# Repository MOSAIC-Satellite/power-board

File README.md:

# Power Board

This is the repository for MOSAIC's Power Board.

For detailed information on the Power Board, check out its core documentation [here](https://www.mosaicsat.org/core_documentation/hardware/power_board/).

To get your own MOSAIC Power Board, visit the MOSAIC fabrication guide [here](https://www.mosaicsat.org/getting_mosaic/).

## Current Features

*Newest board version: 2.0*

| **Feature** |
| :----------- |
| 6x high-side DC sensors for solar cells |
| LiPo battery high side DC sensor |
| Single-cell LiPo battery charger circuit |
| 12x  2mm JST solar cell input jacks|
| 2x 2mm JST battery input jacks |
| LiPo battery overcharge protection |
| Solar cell reverse current protection |
| 2x Qwiic connectors for I2C connection to Main Board |

## Planned Changes

The following are the current plans for changes to MOSAIC's Power Board. 

- The current version of MOSAIC's Power Board is designed to be used with only a single-cell LiPo battery like [this one](https://www.sparkfun.com/lithium-ion-battery-2ah.html). Future iterations of the Power Board should include the option to utilize different energy storage methods, such as AA and 18650 batteries. This, of course, will require a different charger circuit for each method, so the board may include a new slot where users can plug in their preferred power charger circuit. 

## Change Log

You can find the change log for the Power Board on MOSAIC's website [here](https://www.mosaicsat.org/core_documentation/hardware/power_board/change_log/).

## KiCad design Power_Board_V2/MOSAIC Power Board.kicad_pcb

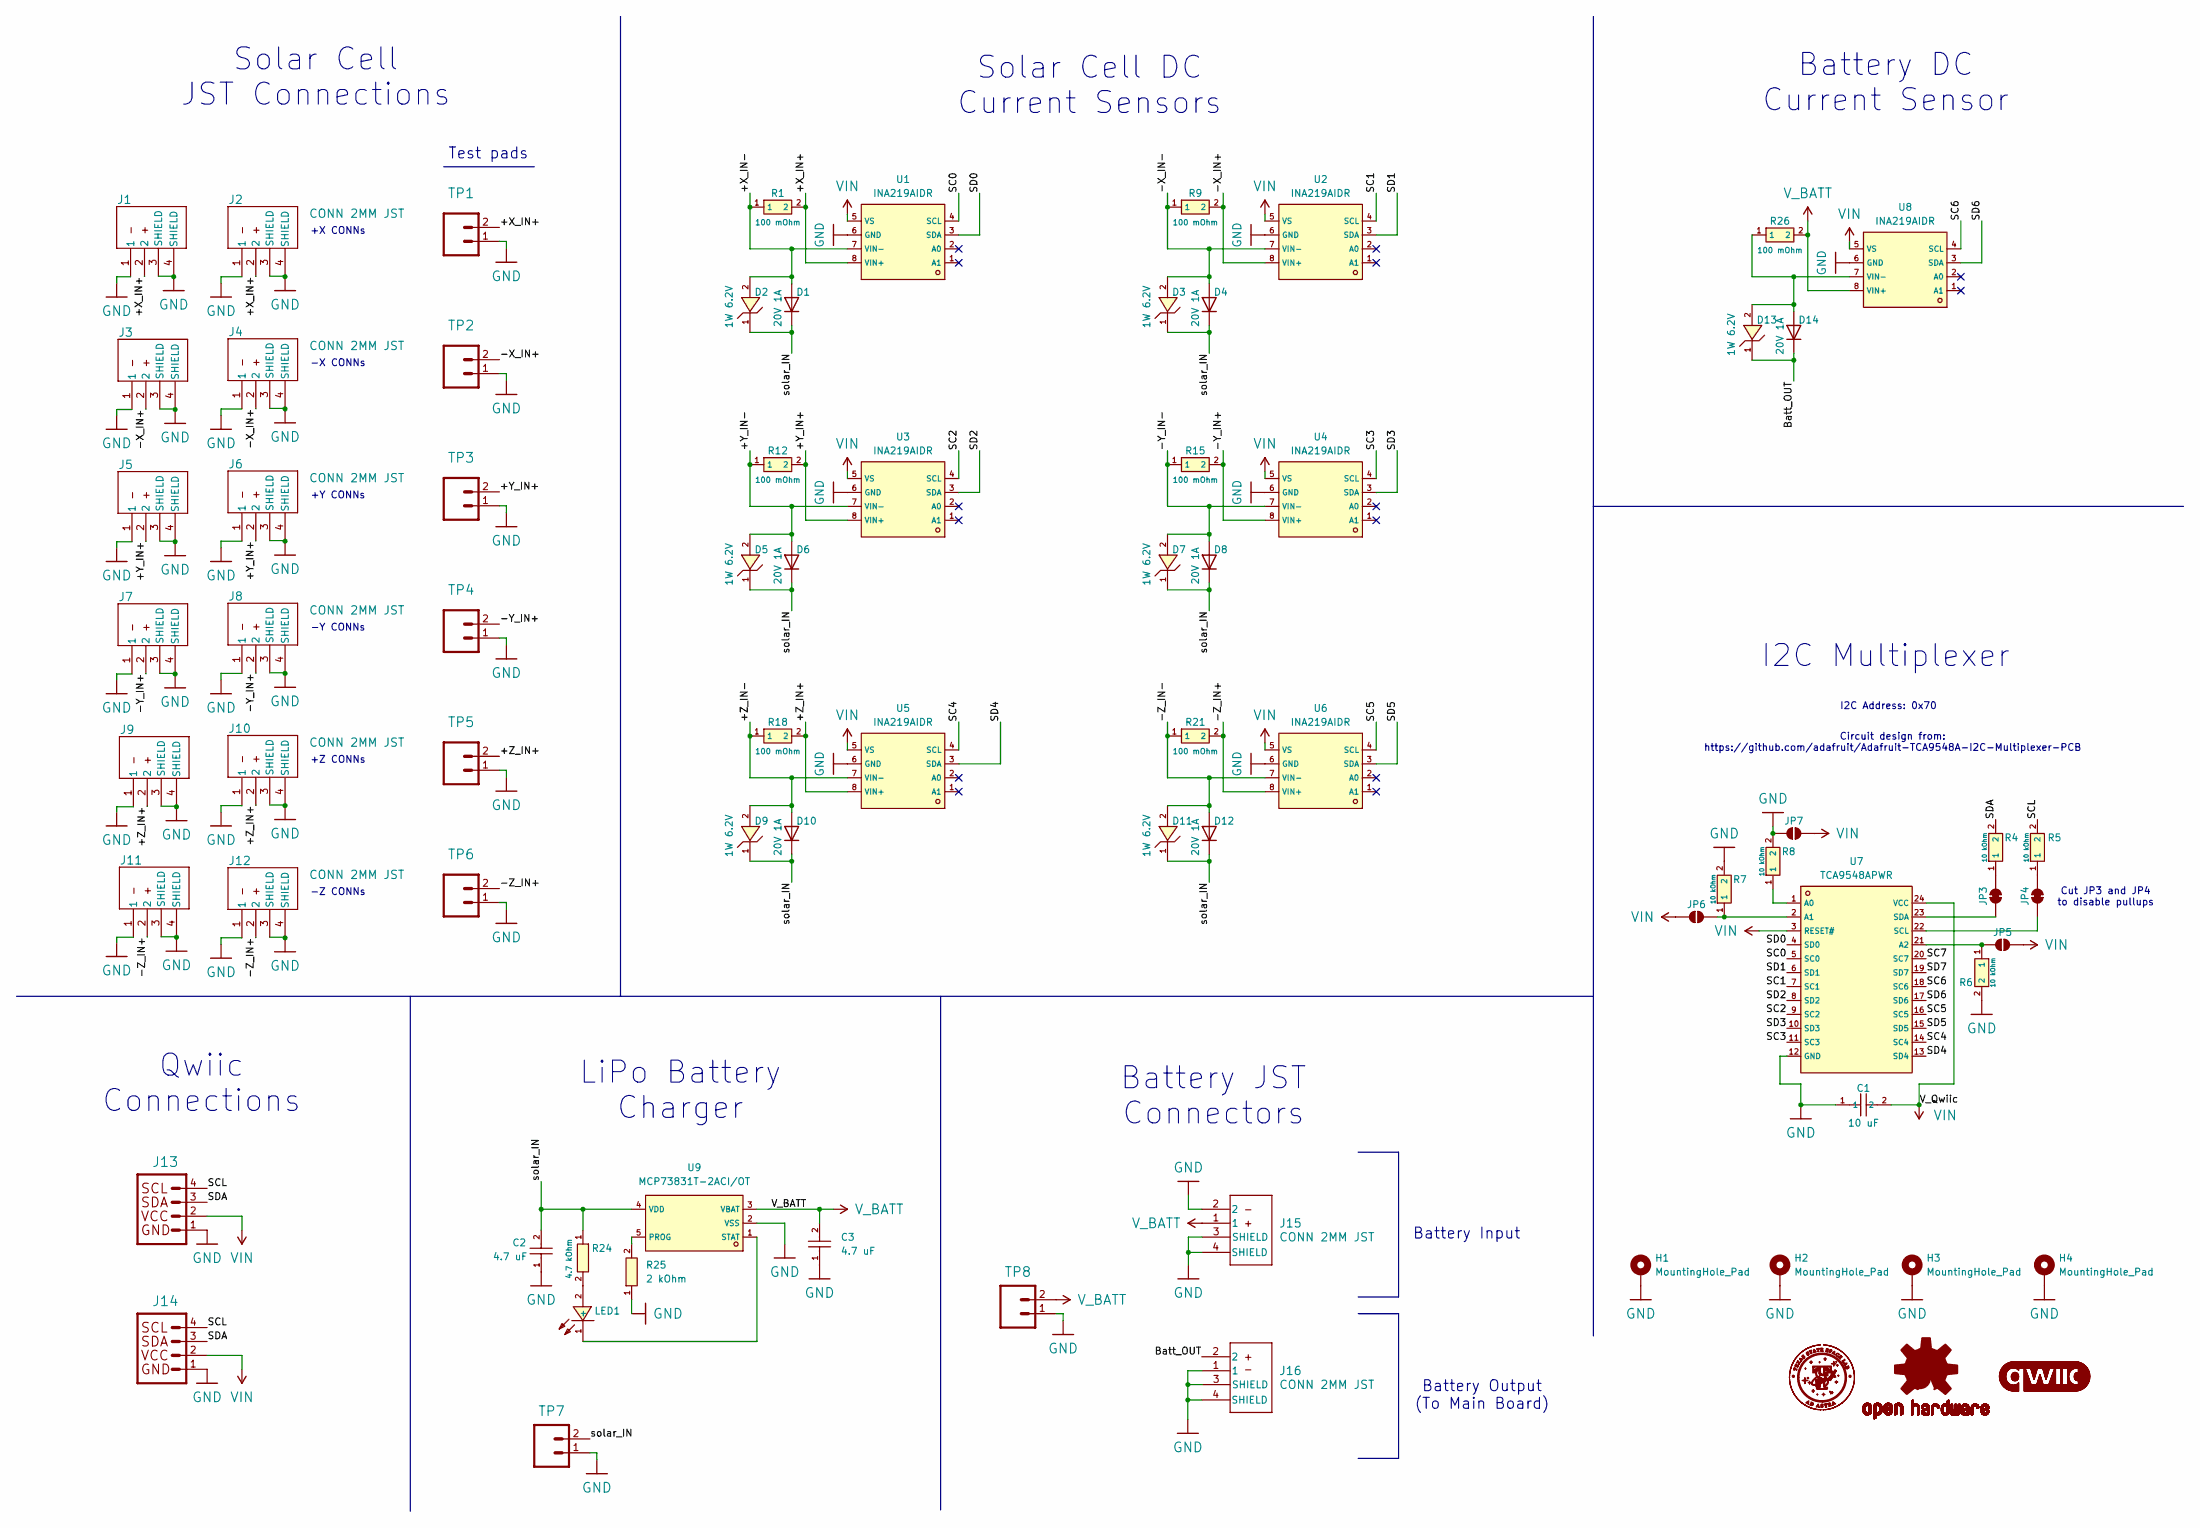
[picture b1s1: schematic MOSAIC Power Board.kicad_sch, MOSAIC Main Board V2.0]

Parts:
C1: 10 uF; C_0603; LCSC C1691
C2, C3: 4.7 uF; C_0603; LCSC C1705
D1, D4, D6, D8, D10, D12, D14: 20V 1A; D_SOD-323; JLCPCB Part # C41424805
D2, D3, D5, D7, D9, D11, D13: 1W 6.2V; Z_DO-214AC; LCSC C151039
H1, H2: MountingHole_Pad; MountingHole_3.2mm_Pad_Oval
H3, H4: MountingHole_Pad; MountingHole_3.2mm_M3_Pad
J1, J2, J3, J4, J5, J6, J7, J8, J9, J10, J11, J12, J15, J16: CONN 2MM JST; CONN_2mm_JST; JLCPCB Part # C295747
J13, J14: QWIIC_CONN_RA; JLCPCB Part # C145956
JP3, JP4: SolderJumper_2_Bridged; SolderJumper-2_P1.3mm_Bridged_RoundedPad1.0x1.5mm
JP5, JP6, JP7: SolderJumper_2_Open; SolderJumper-2_P1.3mm_Open_RoundedPad1.0x1.5mm
LED1: LED_0603; LCSC C125095
LOGO1: OSHW-LOGO-L
LOGO2, LOGO3: QWIIC_logo_8MM
R1, R9, R12, R15, R18, R21, R26: 100 mOhm; R_shunt; LCSC C346817
R4, R5, R6, R7, R8: 10 kOhm; R_0805; LCSC C5123591
R24: 4.7 kOhm; R_0603; LCSC C22874
R25: 2 kOhm; R_0603; LCSC C22975
TP1, TP2, TP3, TP4, TP5, TP6, TP7, TP8: 1X02_NO_SILK
U1, U2, U3, U4, U5, U6, U8: INA219AIDR; LCSC C138706
U7: TCA9548APWR; LCSC C130026
U9: MCP73831T-2ACI/OT; MCP73831_IC_BATT_CNTL; LCSC C424093

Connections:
/+X_IN+: J1.2, J2.2, R1.2, TP1.2, U1.8 (VIN+)
/+X_IN-: D1.2 (A), D2.2, R1.1, U1.7 (VIN-)
/+Y_IN+: J5.2, J6.2, R12.2, TP3.2, U3.8 (VIN+)
/+Y_IN-: D5.2, D6.2 (A), R12.1, U3.7 (VIN-)
/+Z_IN+: J9.2, J10.2, R18.2, TP5.2, U5.8 (VIN+)
/+Z_IN-: D9.2, D10.2 (A), R18.1, U5.7 (VIN-)
/-X_IN+: J3.2, J4.2, R9.2, TP2.2, U2.8 (VIN+)
/-X_IN-: D3.2, D4.2 (A), R9.1, U2.7 (VIN-)
/-Y_IN+: J7.2, J8.2, R15.2, TP4.2, U4.8 (VIN+)
/-Y_IN-: D7.2, D8.2 (A), R15.1, U4.7 (VIN-)
/-Z_IN+: J11.2, J12.2, R21.2, TP6.2, U6.8 (VIN+)
/-Z_IN-: D11.2, D12.2 (A), R21.1, U6.7 (VIN-)
/Batt_OUT: D13.1, D14.1 (K), J16.2
/SC0: U1.4 (SCL), U7.5 (SC0)
/SC1: U2.4 (SCL), U7.7 (SC1)
/SC2: U3.4 (SCL), U7.9 (SC2)
/SC3: U4.4 (SCL), U7.11 (SC3)
/SC4: U5.4 (SCL), U7.14 (SC4)
/SC5: U6.4 (SCL), U7.16 (SC5)
/SC6: U7.18 (SC6), U8.4 (SCL)
/SC7: U7.20 (SC7)
/SCL: J13.4, J14.4, R5.2
/SD0: U1.3 (SDA), U7.4 (SD0)
/SD1: U2.3 (SDA), U7.6 (SD1)
/SD2: U3.3 (SDA), U7.8 (SD2)
/SD3: U4.3 (SDA), U7.10 (SD3)
/SD4: U5.3 (SDA), U7.13 (SD4)
/SD5: U6.3 (SDA), U7.15 (SD5)
/SD6: U7.17 (SD6), U8.3 (SDA)
/SD7: U7.19 (SD7)
/SDA: J13.3, J14.3, R4.2
/solar_IN: C2.2, D1.1 (K), D2.1, D3.1, D4.1 (K), D5.1, D6.1 (K), D7.1, D8.1 (K), D9.1, D10.1 (K), D11.1, D12.1 (K), R24.1, TP7.2, U9.4 (VDD)
GND: C1.1, C2.1, C3.1, H1.1, H2.1, H3.1, H4.1, J1.1, J1.3 (SHIELD), J1.4 (SHIELD), J2.1, J2.3 (SHIELD), J2.4 (SHIELD), J3.1, J3.3 (SHIELD), J3.4 (SHIELD), J4.1, J4.3 (SHIELD), J4.4 (SHIELD), J5.1, J5.3 (SHIELD), J5.4 (SHIELD), J6.1, J6.3 (SHIELD), J6.4 (SHIELD), J7.1, J7.3 (SHIELD), J7.4 (SHIELD), J8.1, J8.3 (SHIELD), J8.4 (SHIELD), J9.1, J9.3 (SHIELD), J9.4 (SHIELD), J10.1, J10.3 (SHIELD), J10.4 (SHIELD), J11.1, J11.3 (SHIELD), J11.4 (SHIELD), J12.1, J12.3 (SHIELD), J12.4 (SHIELD), J13.1, J14.1, J15.2, J15.3 (SHIELD), J15.4 (SHIELD), J16.1, J16.3 (SHIELD), J16.4 (SHIELD), JP7.1 (A), R6.2, R7.2, R8.2, R25.1, TP1.1, TP2.1, TP3.1, TP4.1, TP5.1, TP6.1, TP7.1, TP8.1, U1.6 (GND), U2.6 (GND), U3.6 (GND), U4.6 (GND), U5.6 (GND), U6.6 (GND), U7.12 (GND), U8.6 (GND), U9.2 (VSS)
unnamed: D13.2, D14.2 (A), R26.1, U8.7 (VIN-)
unnamed: JP3.1 (A), U7.23 (SDA)
unnamed: JP3.2 (B), R4.1
unnamed: JP4.1 (A), U7.22 (SCL)
unnamed: JP4.2 (B), R5.1
unnamed: JP5.1 (A), R6.1, U7.21 (A2)
unnamed: JP6.2 (B), R7.1, U7.2 (A1)
unnamed: LED1.2 (+), R24.2
unnamed: LED1.1 (-), U9.1 (STAT)
unnamed: R8.1, U7.1 (A0)
unnamed: R25.2, U9.5 (PROG)
VIN: C1.2, J13.2, J14.2, JP5.2 (B), JP6.1 (A), JP7.2 (B), U1.5 (VS), U2.5 (VS), U3.5 (VS), U4.5 (VS), U5.5 (VS), U6.5 (VS), U7.3 (RESET#), U7.24 (VCC), U8.5 (VS)
V_BATT: C3.2, J15.1, R26.2, TP8.2, U8.8 (VIN+), U9.3 (VBAT)

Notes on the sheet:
Battery Input
-Z CONNs
Battery JST Connectors
Solar Cell JST Connections
Test pads
I2C Multiplexer
-Y CONNs
Circuit design from: https://github.com/adafruit/Adafruit-TCA9548A-I2C-Multiplexer-PCB
+Z CONNs
Battery DC Current Sensor
Qwiic Connections
+X CONNs
+Y CONNs
I2C Address: 0x70
Cut JP3 and JP4 to disable pullups
LiPo Battery Charger
-X CONNs
Battery Output (To Main Board)
Solar Cell DC Current Sensors

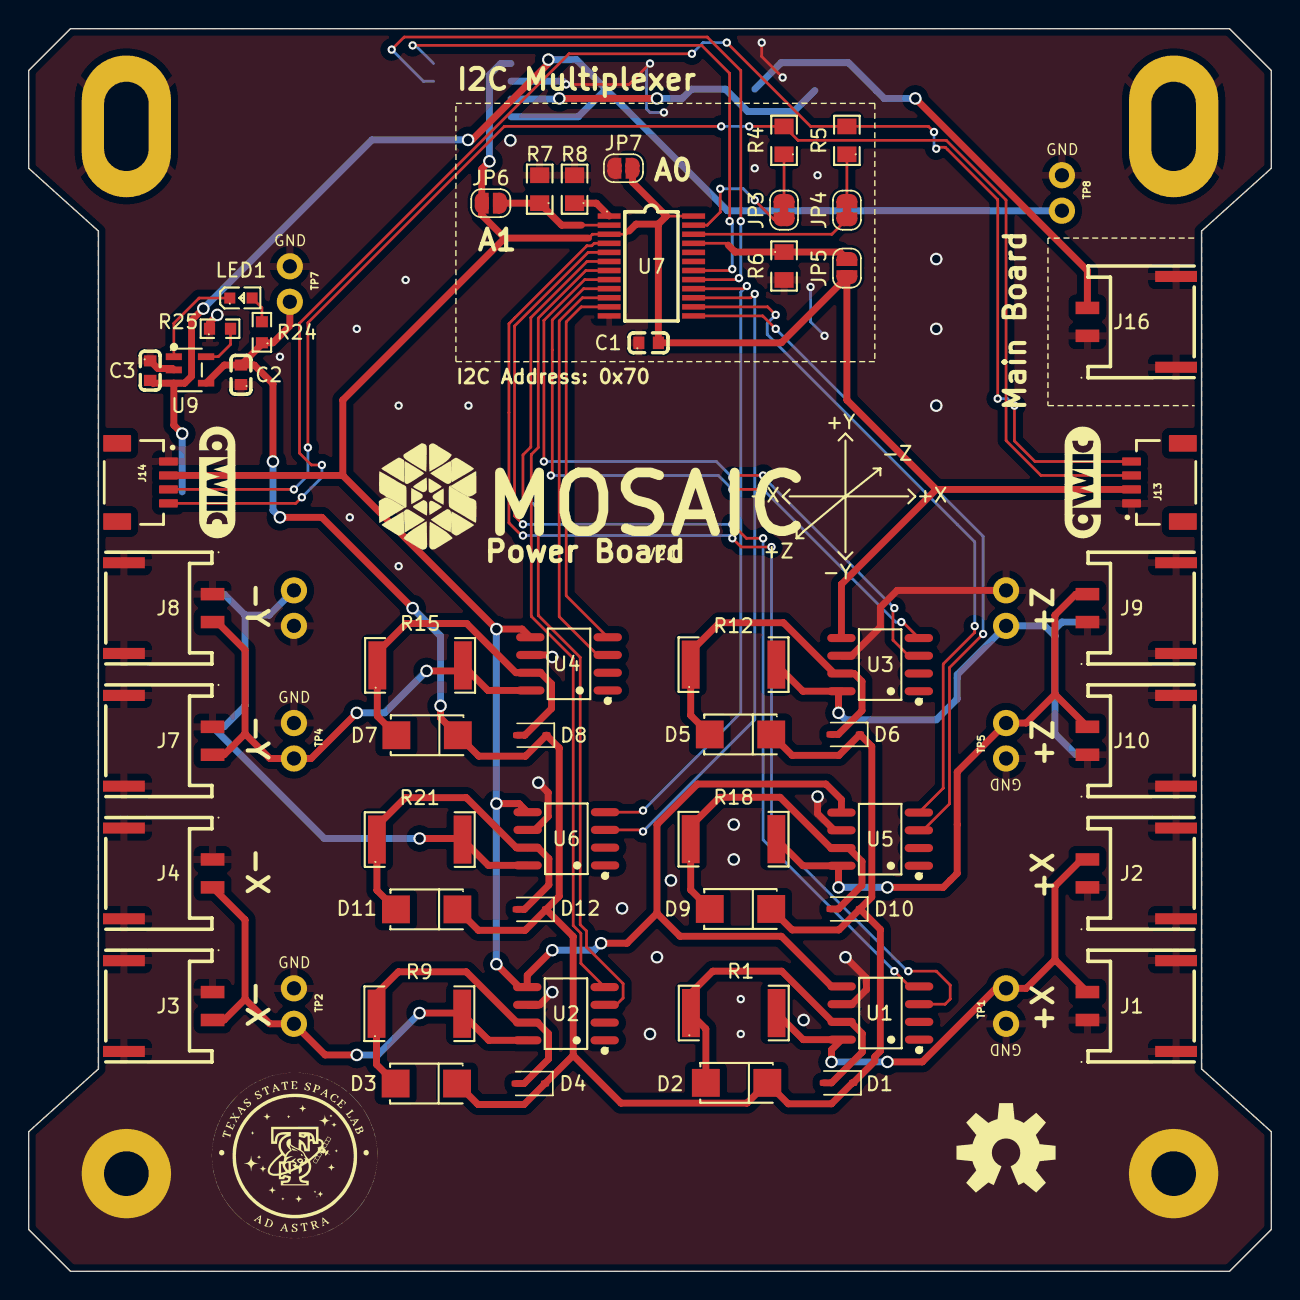
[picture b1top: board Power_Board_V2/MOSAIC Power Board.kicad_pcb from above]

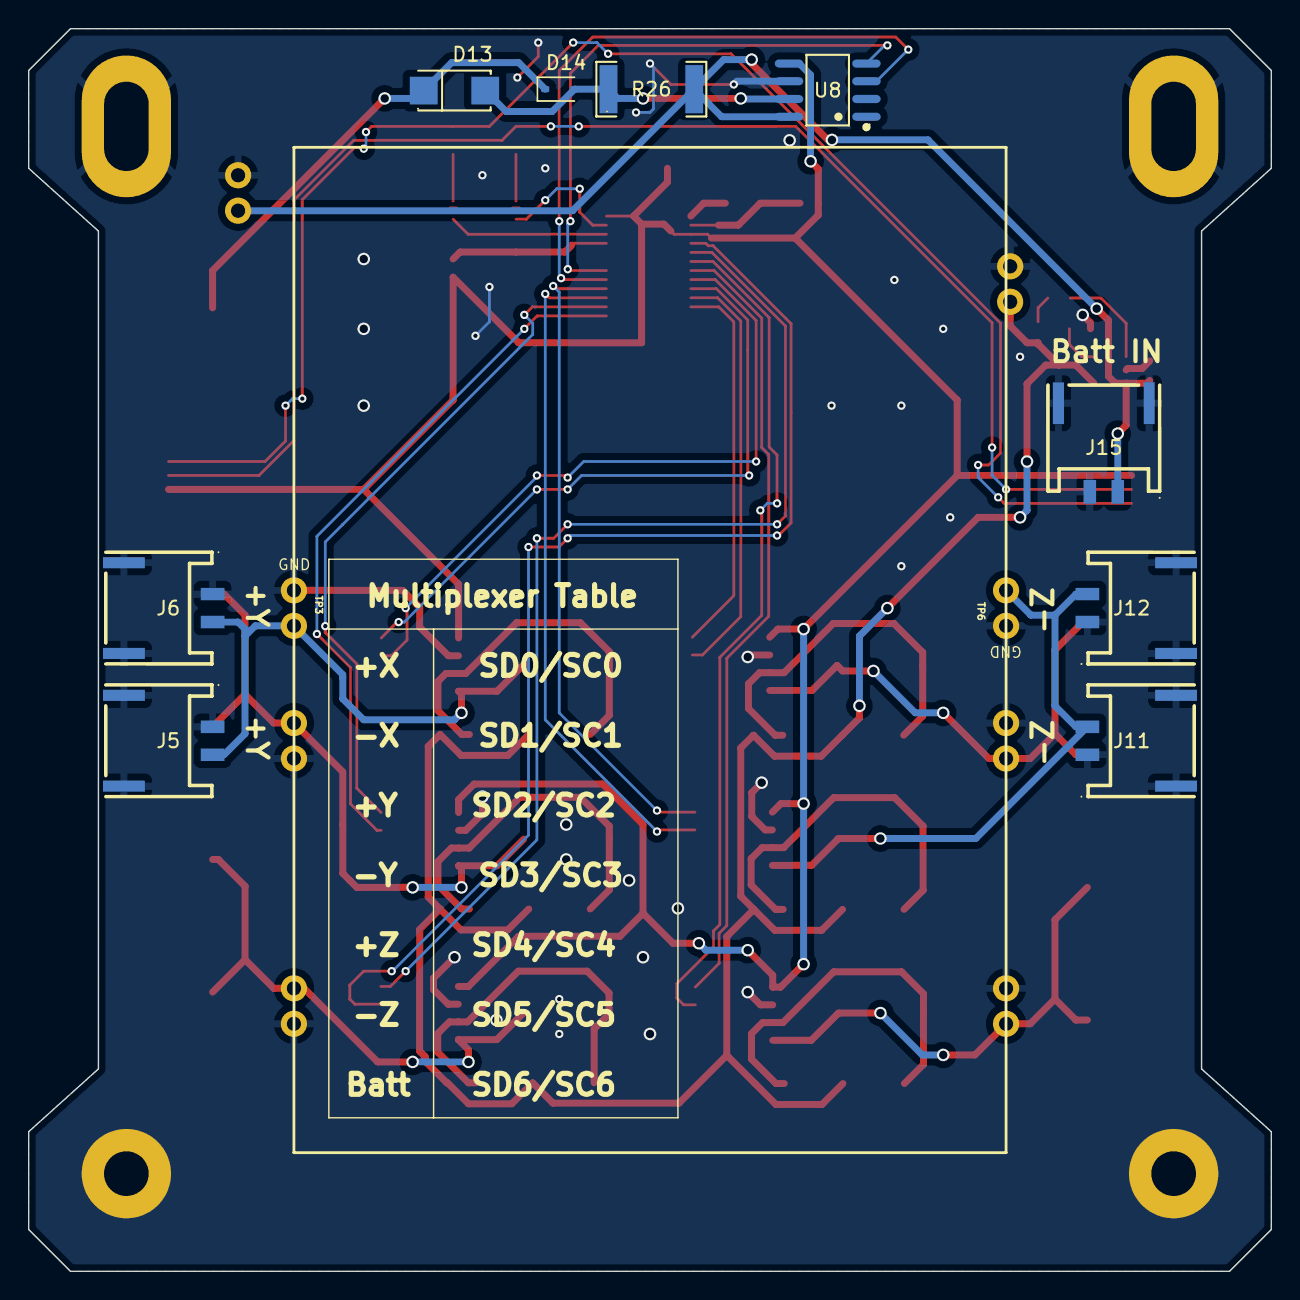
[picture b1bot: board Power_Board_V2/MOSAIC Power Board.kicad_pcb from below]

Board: 2 copper layers, 89.0 x 89.0 mm, 77 parts (11 on the bottom side), 44 nets.

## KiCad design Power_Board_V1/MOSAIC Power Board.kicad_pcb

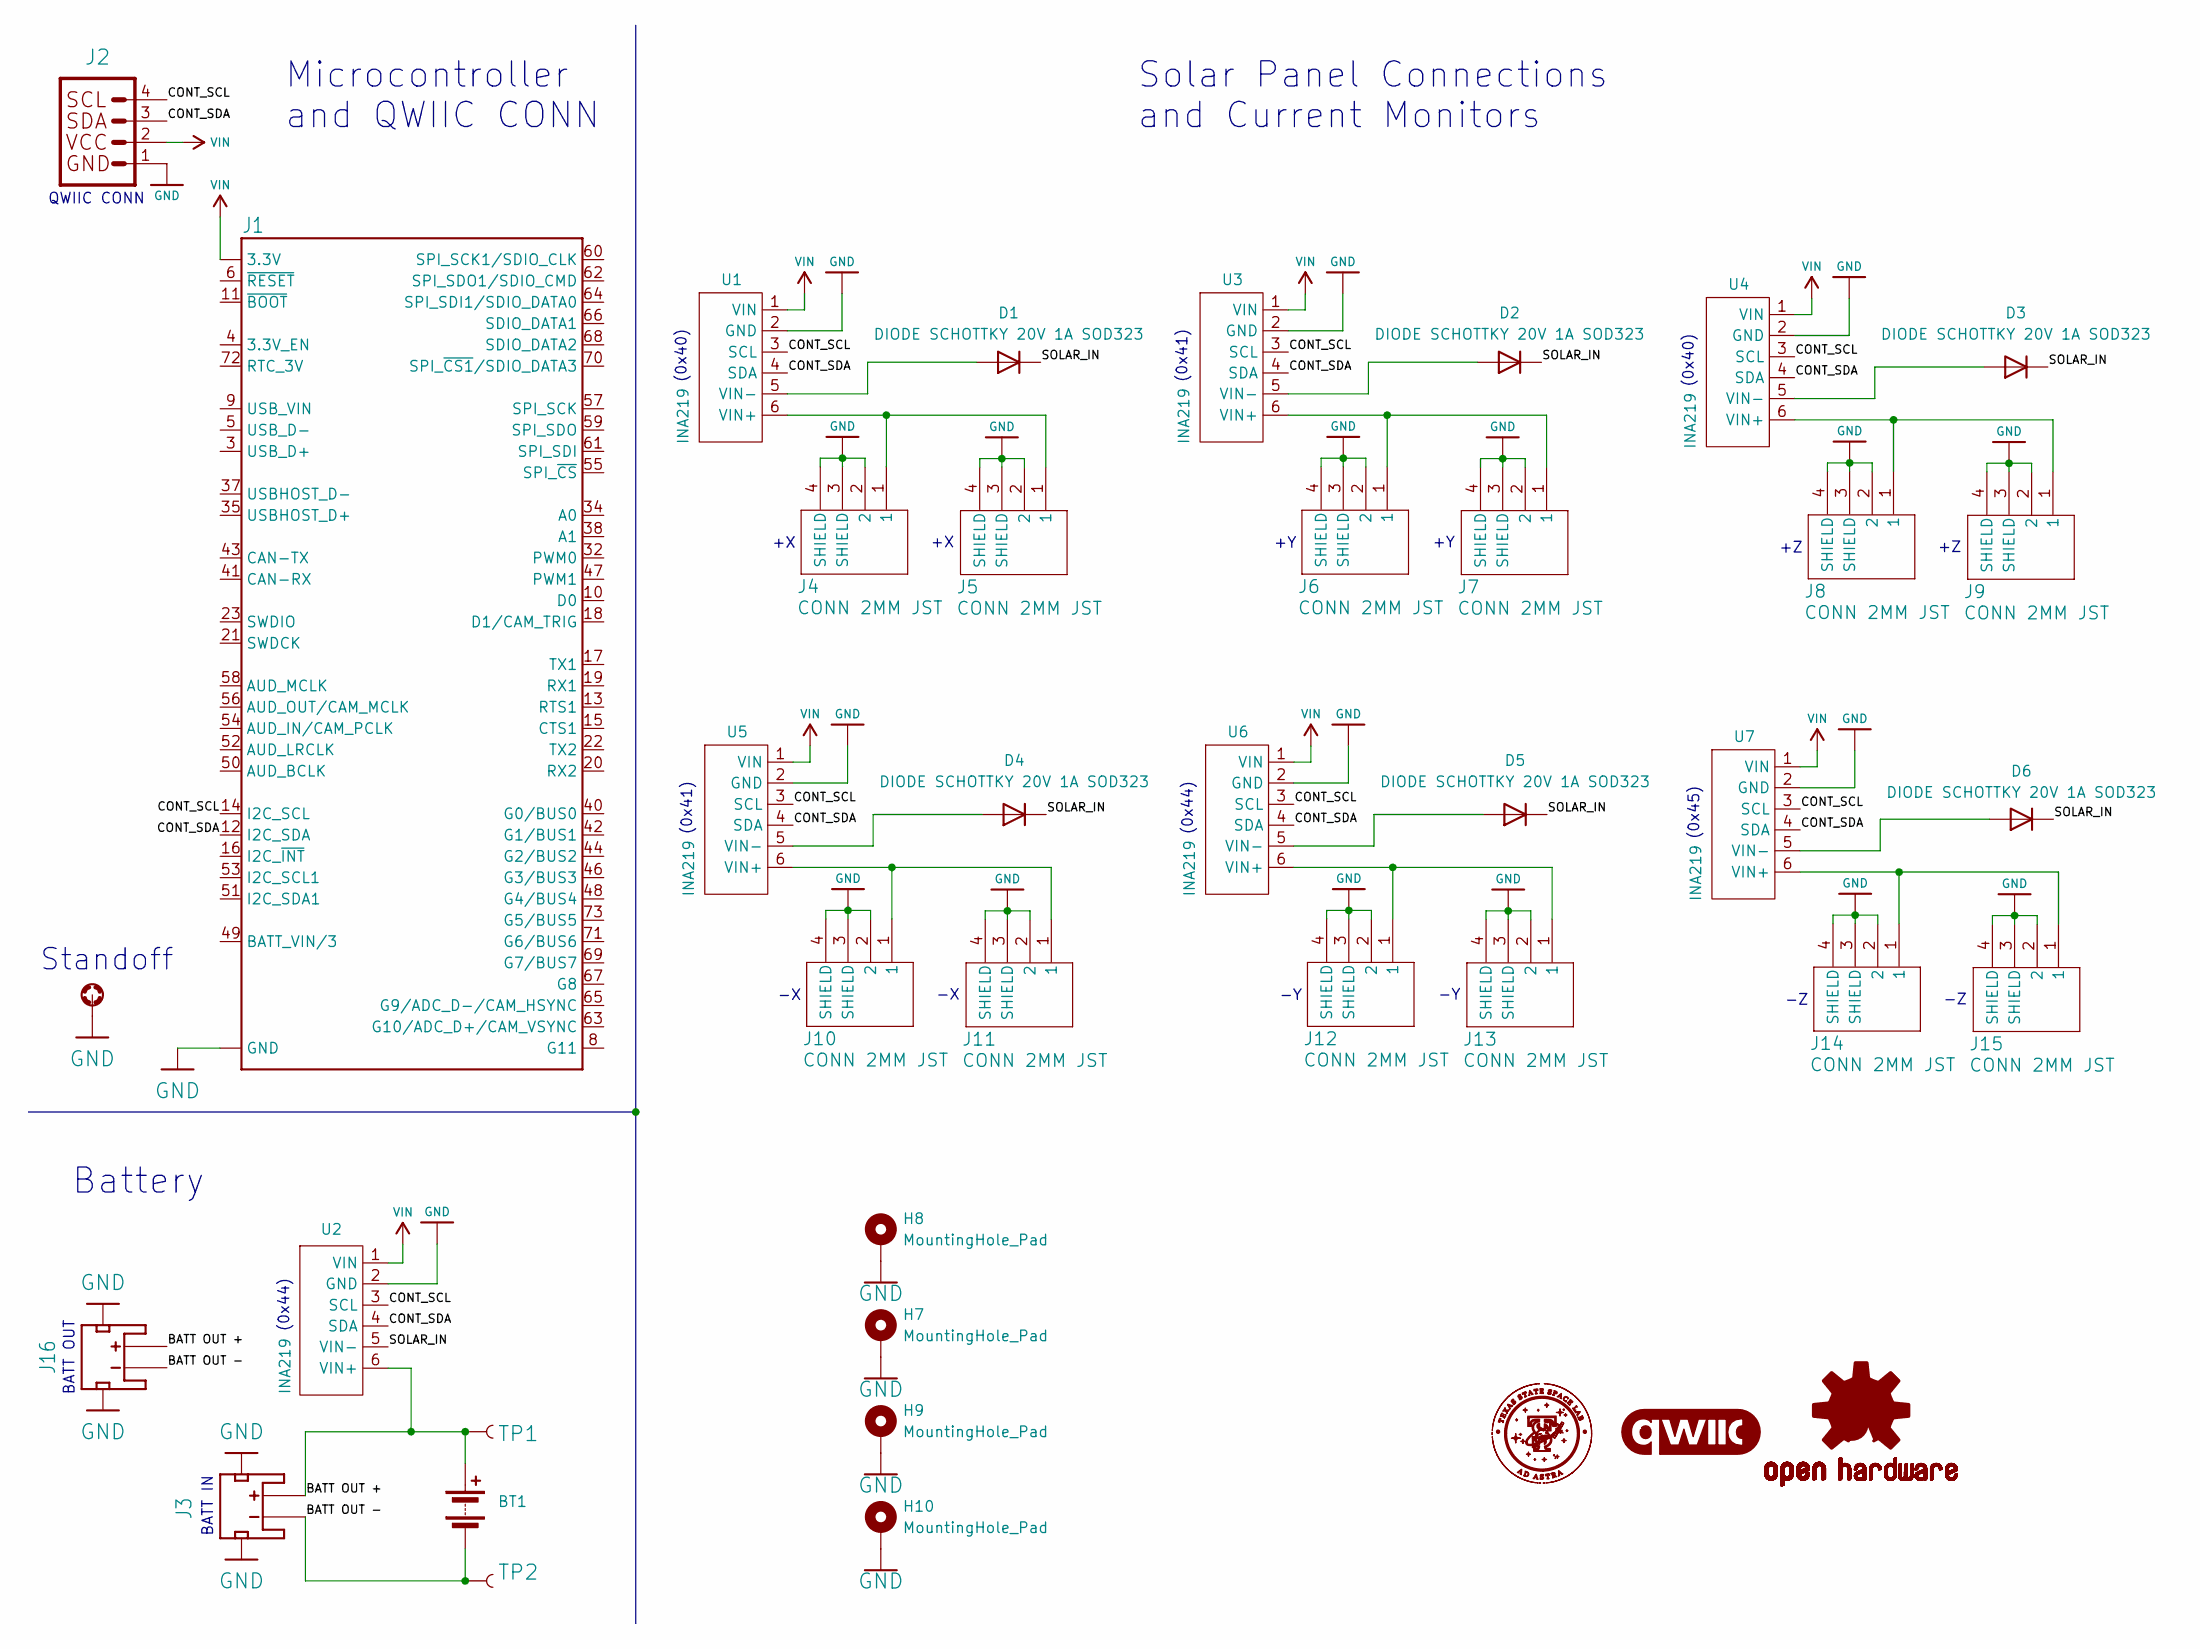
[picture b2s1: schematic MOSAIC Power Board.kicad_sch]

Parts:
BT1: Battery; SparkFun Lithium Ion Battery - 2Ah
D1, D2, D3, D4, D5, D6: DIODE SCHOTTKY 20V 1A SOD323; D_SOD-323; JLCPCB Part # C435857
H1: STAND-OFF-REFLOW-M2.5
H7, H8: MountingHole_Pad; MountingHole_3.2mm_M3_Pad
H9, H10: MountingHole_Pad; MountingHole_3.2mm_Pad_Oval
J1: CONN E; M.2-CONNECTOR-E; JLCPCB Part # C2977809
J2: CONN_QWIIC; JST04_1MM_RA; JLCPCB Part # C145956
J3, J16: CONN_JST_BATT; JST-2-SMD
J4, J5, J6, J7, J8, J9, J10, J11, J12, J13, J14, J15: CONN 2MM JST; CONN_S2B-PH-SM4-TB_JST; JLCPCB Part # C295747
LOGO1: OSHW-LOGO-L
LOGO2: QWIIC_8MM
TP1, TP2: PAD.03X.05
U1, U2, U3, U4, U5, U6, U7: INA219; INA219 Breakout

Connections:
/BATT OUT +: BT1.1 (+), J3.2 (+), J16.2 (+), TP1.1, U2.6 (VIN+)
/BATT OUT -: BT1.2 (-), J3.1 (-), J16.1 (-), TP2.1
/CONT_SCL: J1.14 (I2C_SCL), J2.4, U1.3 (SCL), U2.3 (SCL), U3.3 (SCL), U4.3 (SCL), U5.3 (SCL), U6.3 (SCL), U7.3 (SCL)
/CONT_SDA: J1.12 (I2C_SDA), J2.3, U1.4 (SDA), U2.4 (SDA), U3.4 (SDA), U4.4 (SDA), U5.4 (SDA), U6.4 (SDA), U7.4 (SDA)
/SOLAR_IN: D1.1 (K), D2.1 (K), D3.1 (K), D4.1 (K), D5.1 (K), D6.1 (K), U2.5 (VIN-)
GND: H1.1, H7.1, H8.1, H9.1, H10.1, J1.1 (GND), J1.7 (GND), J1.33 (GND), J1.36 (GND), J1.39 (GND), J1.45 (GND), J1.75 (GND), J2.1, J3.NC1 (PAD1), J3.NC2 (PAD2), J4.2, J4.3 (SHIELD), J4.4 (SHIELD), J5.2, J5.3 (SHIELD), J5.4 (SHIELD), J6.2, J6.3 (SHIELD), J6.4 (SHIELD), J7.2, J7.3 (SHIELD), J7.4 (SHIELD), J8.2, J8.3 (SHIELD), J8.4 (SHIELD), J9.2, J9.3 (SHIELD), J9.4 (SHIELD), J10.2, J10.3 (SHIELD), J10.4 (SHIELD), J11.2, J11.3 (SHIELD), J11.4 (SHIELD), J12.2, J12.3 (SHIELD), J12.4 (SHIELD), J13.2, J13.3 (SHIELD), J13.4 (SHIELD), J14.2, J14.3 (SHIELD), J14.4 (SHIELD), J15.2, J15.3 (SHIELD), J15.4 (SHIELD), J16.NC1 (PAD1), J16.NC2 (PAD2), U1.2 (GND), U2.2 (GND), U3.2 (GND), U4.2 (GND), U5.2 (GND), U6.2 (GND), U7.2 (GND)
unnamed: D1.2 (A), U1.5 (VIN-)
unnamed: D2.2 (A), U3.5 (VIN-)
unnamed: D3.2 (A), U4.5 (VIN-)
unnamed: D4.2 (A), U5.5 (VIN-)
unnamed: D5.2 (A), U6.5 (VIN-)
unnamed: D6.2 (A), U7.5 (VIN-)
unnamed: J4.1, J5.1, U1.6 (VIN+)
unnamed: J6.1, J7.1, U3.6 (VIN+)
unnamed: J8.1, J9.1, U4.6 (VIN+)
unnamed: J10.1, J11.1, U5.6 (VIN+)
unnamed: J12.1, J13.1, U6.6 (VIN+)
unnamed: J14.1, J15.1, U7.6 (VIN+)
VIN: J1.2 (3.3V), J1.74 (3.3V), J2.2, U1.1 (VIN), U2.1 (VIN), U3.1 (VIN), U4.1 (VIN), U5.1 (VIN), U6.1 (VIN), U7.1 (VIN)

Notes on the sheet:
(0x41)
(0x44)
QWIIC CONN
(0x40)
Microcontroller and QWIIC CONN
Solar Panel Connections and Current Monitors
(0x45)
Battery
BATT OUT
BATT IN
Standoff

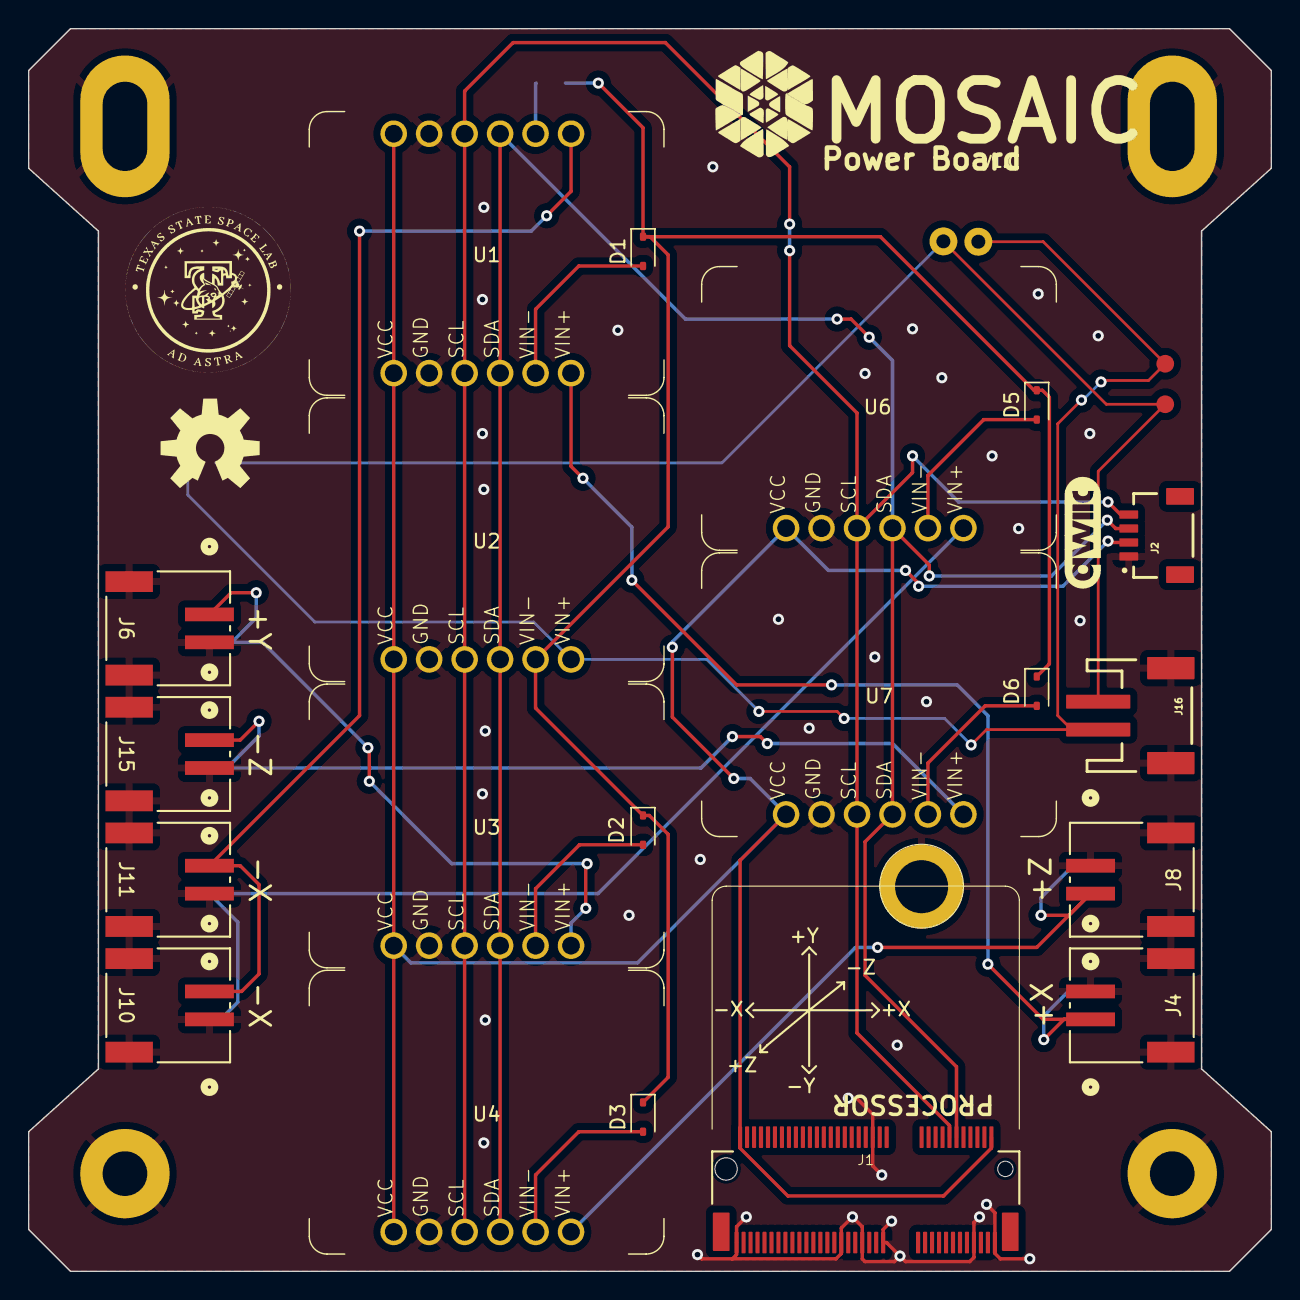
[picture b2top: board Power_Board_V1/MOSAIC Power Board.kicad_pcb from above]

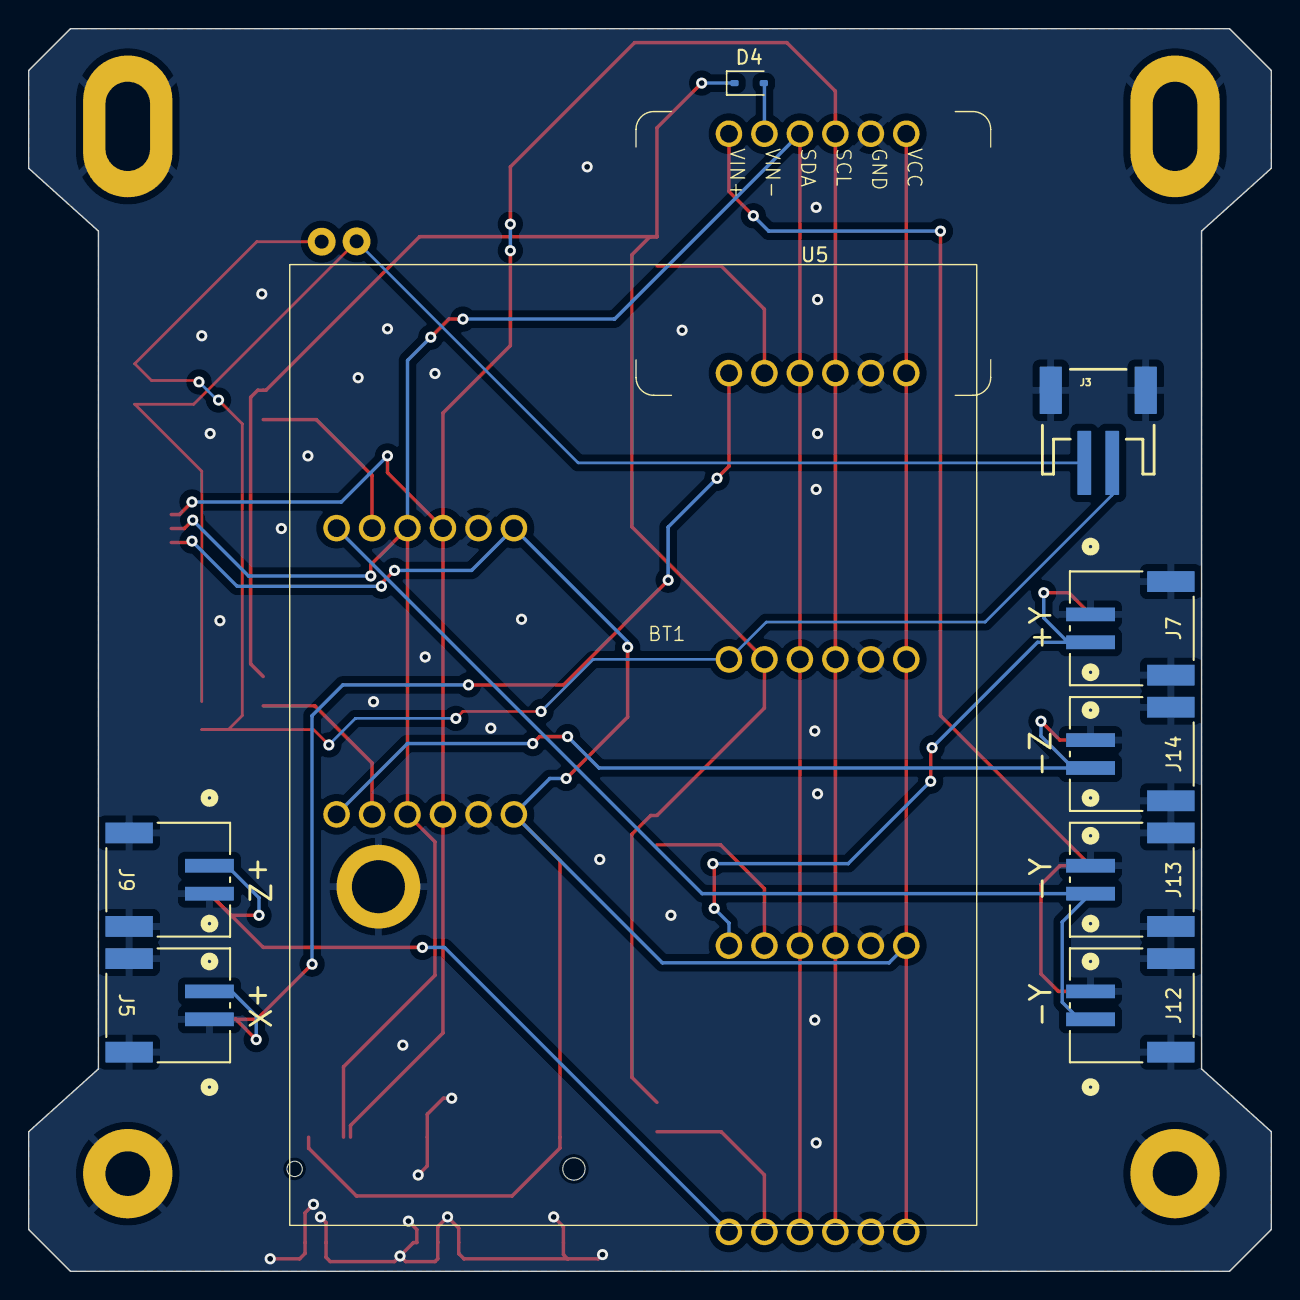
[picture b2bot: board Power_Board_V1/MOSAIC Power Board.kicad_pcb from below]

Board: 2 copper layers, 89.0 x 89.0 mm, 39 parts (10 on the bottom side), 19 nets.

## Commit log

2024-08-07 Create LICENSE.txt
    Created file for non-software copyright license for the Power Board repository for MOSAIC.
2024-08-07 Initial Upload
    Initial upload of files for the MOSAIC Power Board repository.
2025-04-29 Generated a new BOM
2025-04-29 saved changes
2025-04-29 Updated J3, J16 sources
2025-04-29 Updatd J2 Source
2025-04-29 Finished changes
2025-05-30 Work on fixing libraries
2025-05-30 More fixing of libraries
2025-06-10 Placement and routing work
2025-06-12 Finished placement and tracing
2025-06-12 Sourced parts at JLCPCB
2025-06-13 Made JLCPCB production files
2025-07-07 updated i2c addresses for ina219s
2025-07-11 started v2.0
2025-07-11 small adjustment
2025-07-11 work on schematic
2025-07-11 Finished session
2025-07-11 worked on schematic
2025-07-12 work on pcb positioning
2025-07-13 routing work
2025-07-13 finished v2.0
2025-07-17 new production folder
2026-01-09 Updated to replace out of stock comps.
    Zener diodes were out of stock with JLCPCB. Updated production folder to include replacement components.

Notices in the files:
Power_Board_V2/MOSAIC Power Board.kicad_pcb:
Copyright (c) 2022 - 2025
